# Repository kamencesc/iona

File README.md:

# Tested

The code was tested on a prototype board by Stefano Minozzi (cyllboy).

Freel free to contact for questions about code and board.

!! ALERT: It seems that has some issues with Neogeo CD Gamepad, DB15 pin 8 is connected to RAW causing not working correctly. (15/02/2021) !!

# IONA - JVS IO Board by Arduino Pro Micro

Original code by [Takashi Toyoshima](https://github.com/toyoshim).

This program makes an Arduino Pro Micro (With atmega 32u4) work as a JVS IO Board that allows you to connect a legacy JAMMA joystick to a JVS based arcade system, such as NAOMI.

Since now underlying [jvsio](https://github.com/toyoshim/jvsio) library supports several boards and devices, you would be able to run this on other boards with minimal hacks.

Also there is [another example](https://github.com/toyoshim/iona-js) to run iona compatible functionalities without the Arduino firmware.

The USB-HID part for USB Joystick needs [Joystick Library by Matthew Heironimus](https://github.com/MHeironimus/ArduinoJoystickLibrary) and there is how to install it [Installing Additional Arduino Libraries](https://www.arduino.cc/en/guide/libraries).

## Schematic

This program makes an Arduino Pro Micro work as a JVS IO Board that allows youto connect a legacy AES compatible joystick gamepad (included Button 5 and 6 for customomized arcade sticks.

Since now underlying [jvsio](https://github.com/toyoshim/jvsio) library supports several boards and devices, you would be able to run this on other boards with minimal hacks.

Also there is [another example](https://github.com/toyoshim/iona-js) to run iona compatible functionalities without the Arduino firmware.

Resistor (R1) and capacitor (C1) are 100Ohm and 100nF 0603 SMD.

The PCB is based in this DB15 AES compatible pinout:
```
.----------------------------------------------------------------.
\ 1:GND   2:B6    3:CDT   4:B4    5:B2    6:RGH   7:DWN   8:+5V  /
 \                                                              /
  \  9:NC   10:B5   11:STR    12:B3   13:B1   14:LFT    15:UP  /
    `---------------------------------------------------------´
```
The Board  has a jumper, if it's shorted then it works as a USB Stick for a computer, using the micro USB of Arduino., else it works aas a JVS for the naomi using the USB B connector.

In JVS mode, the Naomi's USB doesn't give power to the board, use the micro USB connector or the power jumpers on the board (See legend on the back side of the PCB). You can get 5V from CN7 on the Naomi Board.
```
 _________________
| 5V  5V  GND GND |   CN7
 ¯¯¯¯¯¯¯¯¯¯¯¯¯¯¯¯¯
```
!! Be careful with your Pro Micro's voltage config, jumper J1 needs to be set at 5V !!
## Board (PCB)

The GND pins from the arduino are marked in white, and there's an indication of USB and J1 position.

Be sure that you mount the pinheader on the component side of the arduino:

## !! Use an Arduino Pro Micro with micro USB connector, the mini USB version is a little wider) !! ##

And, the pins go up, the PCB is used like a regular Shield.

Note: JVS uses the USB connector, but it isn't the real USB at all.
The protocol is completely different, and it does not provide the 5V power.

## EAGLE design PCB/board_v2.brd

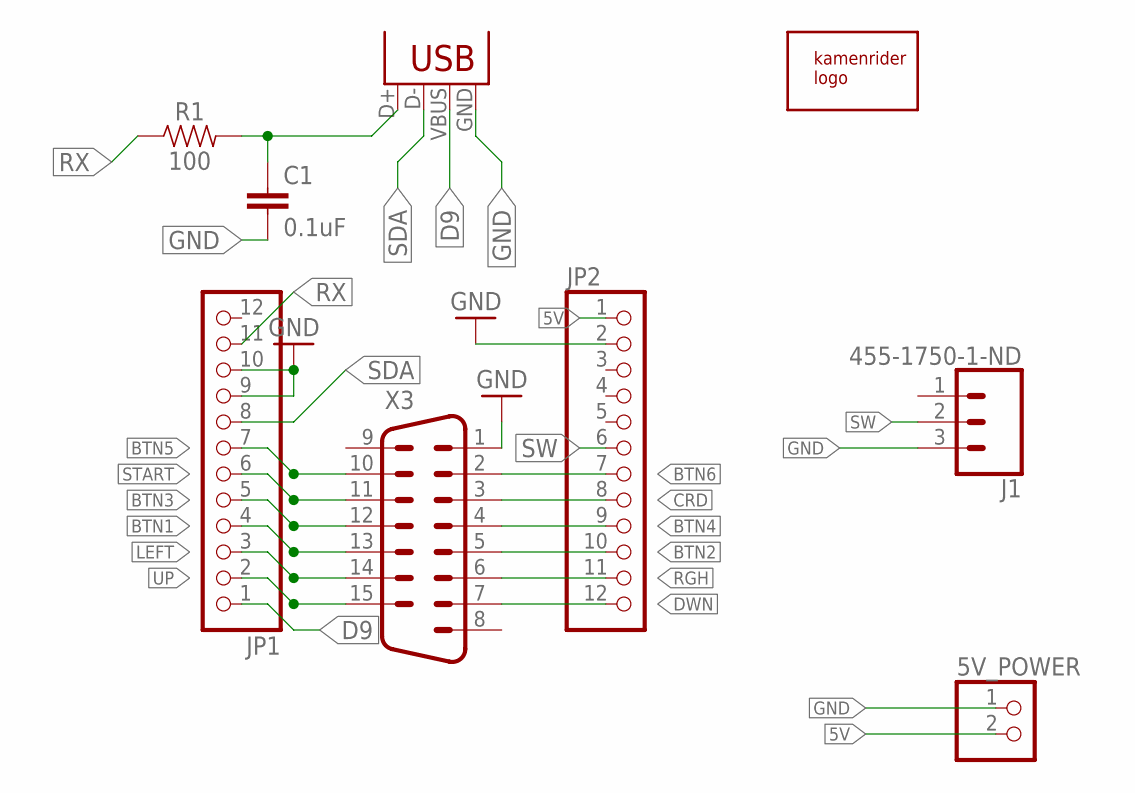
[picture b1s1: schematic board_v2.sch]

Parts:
5V_POWER: PINHD-1X02_2.54-S; 1X02-S
C1: 0.1uF; 0603
J1: 455-1750-1-ND; 1X03
JP1, JP2: PINHD-1X12; 1X12
R1: 100; 0603
U$1: KAMENRIDER_LOGOV2_COLOR_OPAC; 10_6_V2
X2: USB-B-H
X3: M15V

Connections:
5V: 5V_POWER.2, JP2.1
BTN1: JP1.4, X3.13
BTN2: JP2.10, X3.5
BTN3: JP1.5, X3.12
BTN4: JP2.9, X3.4
BTN5: JP1.7, X3.10
BTN6: JP2.7, X3.2
CRD: JP2.8, X3.3
D9: JP1.1, X2.VBUS
DWN: JP2.12, X3.7
GND: 5V_POWER.1, C1.2, J1.3, JP1.9, JP1.10, JP2.2, X2.GND, X3.1
LEFT: JP1.3, X3.14
RGH: JP2.11, X3.6
RX: JP1.11, R1.1
RX_R: C1.1, R1.2, X2.D+
SDA: JP1.8, X2.D-
START: JP1.6, X3.11
SW: J1.2, JP2.6
UP: JP1.2, X3.15

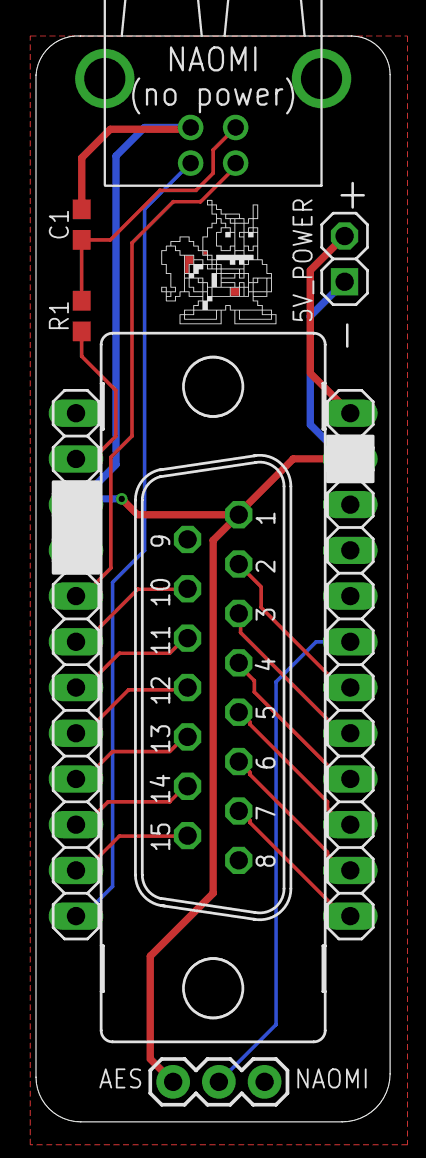
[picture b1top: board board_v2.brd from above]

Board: 2 copper layers, 19.7 x 60.3 mm, 9 parts (0 on the bottom side), 19 nets.

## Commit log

2021-02-14 Update README.md
    Some extra info about the Joystick Library by Matthew Heironimus, how to get and how to install it.
2021-02-15 Update README.md
    Added info about an issue with neogeo cd gamepad.
2021-02-24 Add files via upload
    New PCB
2021-02-24 Rename Placa V1.brd to board_v2.brd
2021-02-24 Rename Placa V1.sch to board_v2.sch
2021-04-09 Update README.md
    Info about pins on the Arduino.
2021-05-06 Add files via upload
    3d board about how to assemble
2021-05-06 Add files via upload
    resize

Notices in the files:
parts and their libraries:
SparkFun-Connectors: Licensing: Creative Commons ShareAlike 4.0 International - https://creativecommons.org/licenses/by-sa/4.0
